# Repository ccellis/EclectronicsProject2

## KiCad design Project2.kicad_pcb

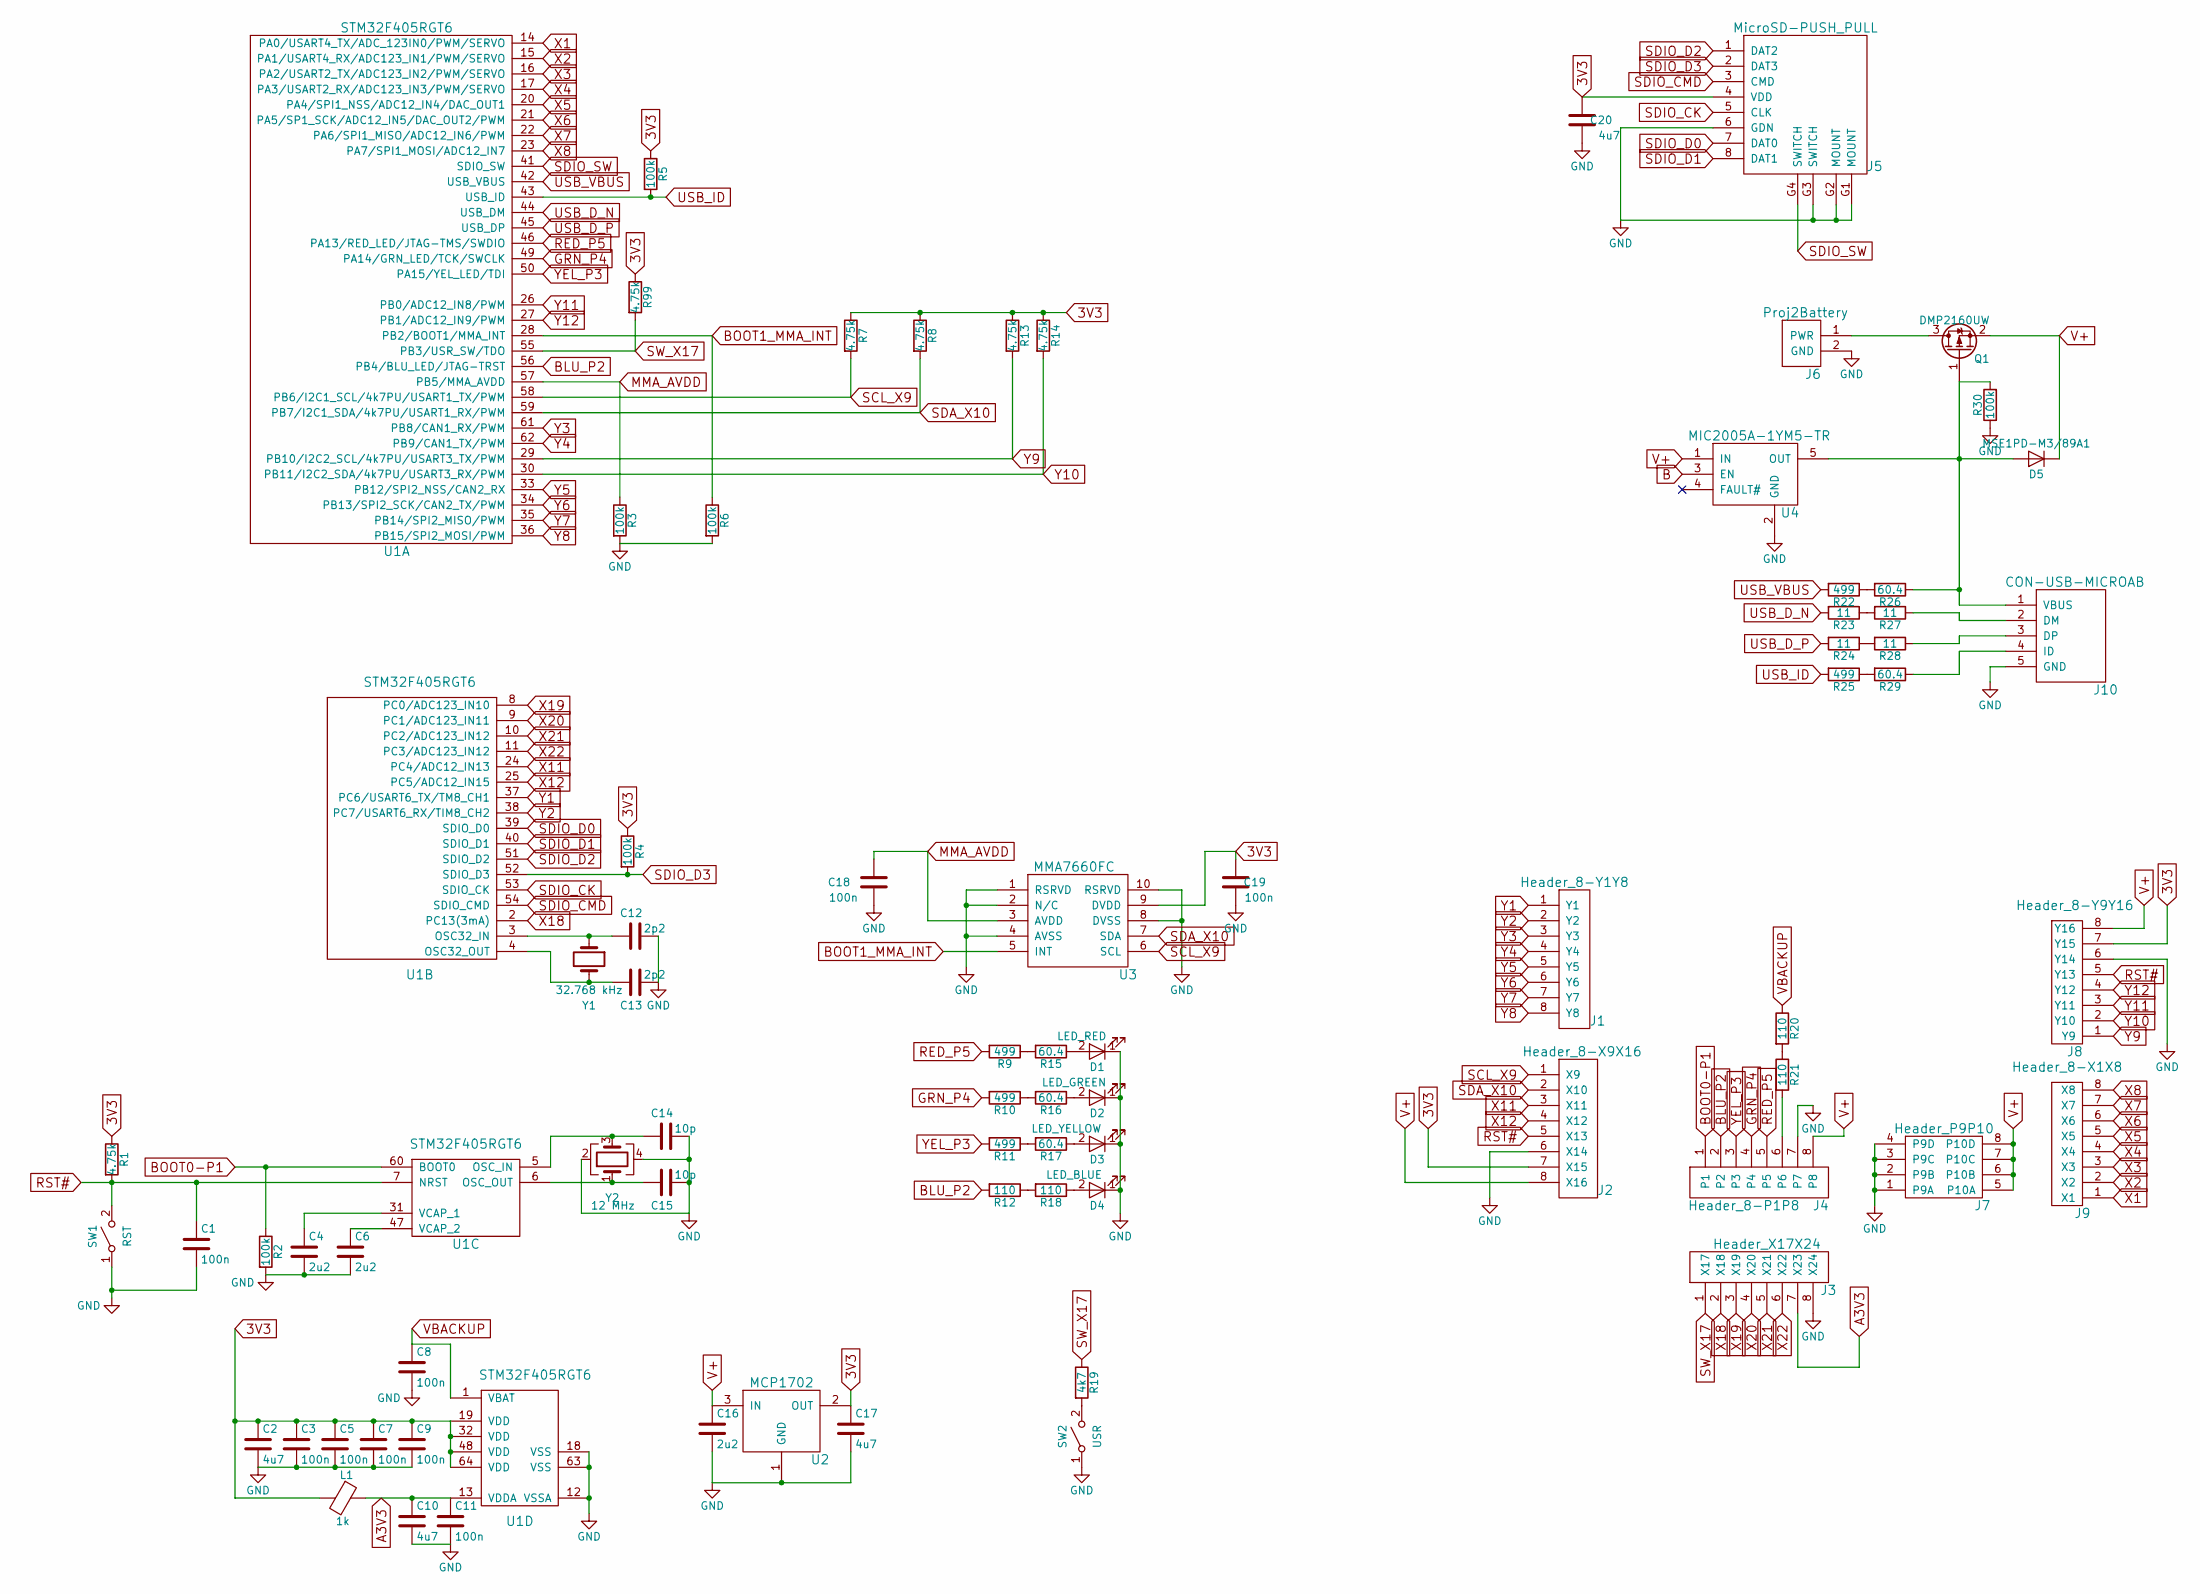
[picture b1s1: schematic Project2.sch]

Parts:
C1, C3, C5, C7, C8, C9, C11, C18, C19: 100n; C_0603
C2, C10, C17, C20: 4u7; C_0603
C4, C6, C16: 2u2; C_0603
C12, C13: 2p2; C_0603
C14, C15: 10p; C_0603
D1: LED_RED; LED_0805
D2: LED_GREEN; LED_0805
D3: LED_YELLOW; LED_0805
D4: LED_BLUE; LED_0805
D5: MSE1PD-M3/89A1; Diode
J1: Header_8-Y1Y8; 1x8_Header
J2: Header_8-X9X16; 1x8_Header
J3: Header_X17X24; 1x8_Header
J4: Header_8-P1P8; 1x8_Header
J5: MicroSD-PUSH_PULL; MicroSD
J6: Proj2Battery; Battery
J7: Header_P9P10; 2x4_Header
J8: Header_8-Y9Y16; 1x8_Header
J9: Header_8-X1X8; 1x8_Header
J10: CON-USB-MICROAB; USB_microB_2040002-1
L1: 1k; L_0603
Q1: DMP2160UW; MOSFET
R1, R7, R8, R13, R14, R99: 4.75k; R_0603
R2, R3, R4, R5, R6, R30: 100k; R_0603
R9, R10, R11, R22, R25: 499; R_0603
R12, R18, R20, R21: 110; R_0603
R15, R16, R17, R26, R29: 60.4; R_0603
R19: 4k7; R_0603
R23, R24, R27, R28: 11; R_0603
SW1: RST; Switch
SW2: USR; Switch
U1: STM32F405RGT6; MicrocontrollerFootprint
U2: MCP1702; VoltageRegulator
U3: MMA7660FC; Accelerometer
U4: MIC2005A-1YM5-TR; SOT-23-5
Y1: 32.768 kHz; Crystal_SMD_3215-2pin_3.2x1.5mm
Y2: 12 MHz; Crystal_SMD_3225-4pin_3.2x2.5mm

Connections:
3V3: C2.1, C3.1, C5.1, C7.1, C9.1, C17.1, C19.2, C20.2, J2.7 (X15), J5.4 (VDD), J8.7 (Y15), L1.2, R1.1, R4.1, R5.1, R7.1, R8.1, R13.1, R14.1, R99.1, U1.19 (VDD), U1.32 (VDD), U1.48 (VDD), U1.64 (VDD), U2.2 (OUT), U3.9 (DVDD)
A3V3: C10.1, C11.1, J3.7 (X23), L1.1, U1.13 (VDDA)
B: U4.3 (EN)
BLU_P2: J4.2, R12.2, U1.56 (PB4/BLU_LED/JTAG-TRST)
BOOT0-P1: J4.1, R2.1, U1.60 (BOOT0)
BOOT1_MMA_INT: R6.1, U1.28 (PB2/BOOT1/MMA_INT), U3.5 (INT)
GND: C1.2, C2.2, C3.2, C4.2, C5.2, C6.2, C7.2, C8.2, C9.2, C10.2, C11.2, C12.2, C13.2, C14.2, C15.2, C16.2, C17.2, C18.1, C19.1, C20.1, D1.1 (K), D2.1 (K), D3.1 (K), D4.1 (K), J2.6 (X14), J3.8 (X24), J4.7, J5.6 (GDN), J5.G1 (MOUNT), J5.G2 (MOUNT), J5.G3 (SWITCH), J6.2 (GND), J7.1 (P9A), J7.2 (P9B), J7.3 (P9C), J7.4 (P9D), J8.6 (Y14), J10.5 (GND), R2.2, R3.2, R6.2, R30.1, SW1.1 (A), SW2.1 (A), U1.12 (VSSA), U1.18 (VSS), U1.63 (VSS), U2.1 (GND), U3.1 (RSRVD), U3.2 (N/C), U3.4 (AVSS), U3.8 (DVSS), U3.10 (RSRVD), U4.2 (GND), Y2.2, Y2.4
GRN_P4: J4.4, R10.2, U1.49 (PA14/GRN_LED/TCK/SWCLK)
MMA_AVDD: C18.2, R3.1, U1.57 (PB5/MMA_AVDD), U3.3 (AVDD)
unnamed: C4.1, U1.31 (VCAP_1)
unnamed: C6.1, U1.47 (VCAP_2)
unnamed: C12.1, U1.3 (OSC32_IN), Y1.1
unnamed: C13.1, U1.4 (OSC32_OUT), Y1.2
unnamed: C14.1, U1.5 (OSC_IN), Y2.3
unnamed: C15.1, U1.6 (OSC_OUT), Y2.1
unnamed: D1.2 (A), R15.1
unnamed: D2.2 (A), R16.1
unnamed: D3.2 (A), R17.1
unnamed: D4.2 (A), R18.1
unnamed: D5.2 (A), J10.1 (VBUS), Q1.1 (G), R26.1, R30.2, U4.5 (OUT)
unnamed: J4.6, R21.2
unnamed: J6.1 (PWR), Q1.3 (D)
unnamed: J10.2 (DM), R27.1
unnamed: J10.3 (DP), R28.1
unnamed: J10.4 (ID), R29.1
unnamed: R10.1, R16.2
unnamed: R11.1, R17.2
unnamed: R12.1, R18.2
unnamed: R9.1, R15.2
unnamed: R19.2, SW2.2 (B)
unnamed: R20.2, R21.1
unnamed: R22.1, R26.2
unnamed: R23.1, R27.2
unnamed: R24.1, R28.2
unnamed: R25.1, R29.2
RED_P5: J4.5, R9.2, U1.46 (PA13/RED_LED/JTAG-TMS/SWDIO)
RST#: C1.1, J2.5 (X13), J8.5 (Y13), R1.2, SW1.2 (B), U1.7 (NRST)
SCL_X9: J2.1 (X9), R7.2, U1.58 (PB6/I2C1_SCL/4k7PU/USART1_TX/PWM), U3.6 (SCL)
SDA_X10: J2.2 (X10), R8.2, U1.59 (PB7/I2C1_SDA/4k7PU/USART1_RX/PWM), U3.7 (SDA)
SDIO_CK: J5.5 (CLK), U1.53 (SDIO_CK)
SDIO_CMD: J5.3 (CMD), U1.54 (SDIO_CMD)
SDIO_D0: J5.7 (DAT0), U1.39 (SDIO_D0)
SDIO_D1: J5.8 (DAT1), U1.40 (SDIO_D1)
SDIO_D2: J5.1 (DAT2), U1.51 (SDIO_D2)
SDIO_D3: J5.2 (DAT3), R4.2, U1.52 (SDIO_D3)
SDIO_SW: J5.G4 (SWITCH), U1.41 (SDIO_SW)
SW_X17: J3.1 (X17), R19.1, R99.2, U1.55 (PB3/USR_SW/TDO)
USB_D_N: R23.2, U1.44 (USB_DM)
USB_D_P: R24.2, U1.45 (USB_DP)
USB_ID: R5.2, R25.2, U1.43 (USB_ID)
USB_VBUS: R22.2, U1.42 (USB_VBUS)
V+: C16.1, D5.1 (K), J2.8 (X16), J4.8, J7.5 (P10A), J7.6 (P10B), J7.7 (P10C), J7.8 (P10D), J8.8 (Y16), Q1.2 (S), U2.3 (IN), U4.1 (IN)
VBACKUP: C8.1, R20.1, U1.1 (VBAT)
X1: J9.1 (X1), U1.14 (PA0/USART4_TX/ADC_123IN0/PWM/SERVO)
X2: J9.2 (X2), U1.15 (PA1/USART4_RX/ADC123_IN1/PWM/SERVO)
X3: J9.3 (X3), U1.16 (PA2/USART2_TX/ADC123_IN2/PWM/SERVO)
X4: J9.4 (X4), U1.17 (PA3/USART2_RX/ADC123_IN3/PWM/SERVO)
X5: J9.5 (X5), U1.20 (PA4/SPI1_NSS/ADC12_IN4/DAC_OUT1)
X6: J9.6 (X6), U1.21 (PA5/SP1_SCK/ADC12_IN5/DAC_OUT2/PWM)
X7: J9.7 (X7), U1.22 (PA6/SPI1_MISO/ADC12_IN6/PWM)
X8: J9.8 (X8), U1.23 (PA7/SPI1_MOSI/ADC12_IN7)
X11: J2.3 (X11), U1.24 (PC4/ADC12_IN13)
X12: J2.4 (X12), U1.25 (PC5/ADC12_IN15)
X18: J3.2 (X18), U1.2 (PC13(3mA))
X19: J3.3 (X19), U1.8 (PC0/ADC123_IN10)
X20: J3.4 (X20), U1.9 (PC1/ADC123_IN11)
X21: J3.5 (X21), U1.10 (PC2/ADC123_IN12)
X22: J3.6 (X22), U1.11 (PC3/ADC123_IN12)
Y1: J1.1 (Y1), U1.37 (PC6/USART6_TX/TM8_CH1)
Y2: J1.2 (Y2), U1.38 (PC7/USART6_RX/TIM8_CH2)
Y3: J1.3 (Y3), U1.61 (PB8/CAN1_RX/PWM)
Y4: J1.4 (Y4), U1.62 (PB9/CAN1_TX/PWM)
Y5: J1.5 (Y5), U1.33 (PB12/SPI2_NSS/CAN2_RX)
Y6: J1.6 (Y6), U1.34 (PB13/SPI2_SCK/CAN2_TX/PWM)
Y7: J1.7 (Y7), U1.35 (PB14/SPI2_MISO/PWM)
Y8: J1.8 (Y8), U1.36 (PB15/SPI2_MOSI/PWM)
Y9: J8.1 (Y9), R13.2, U1.29 (PB10/I2C2_SCL/4k7PU/USART3_TX/PWM)
Y10: J8.2 (Y10), R14.2, U1.30 (PB11/I2C2_SDA/4k7PU/USART3_RX/PWM)
Y11: J8.3 (Y11), U1.26 (PB0/ADC12_IN8/PWM)
Y12: J8.4 (Y12), U1.27 (PB1/ADC12_IN9/PWM)
YEL_P3: J4.3, R11.2, U1.50 (PA15/YEL_LED/TDI)

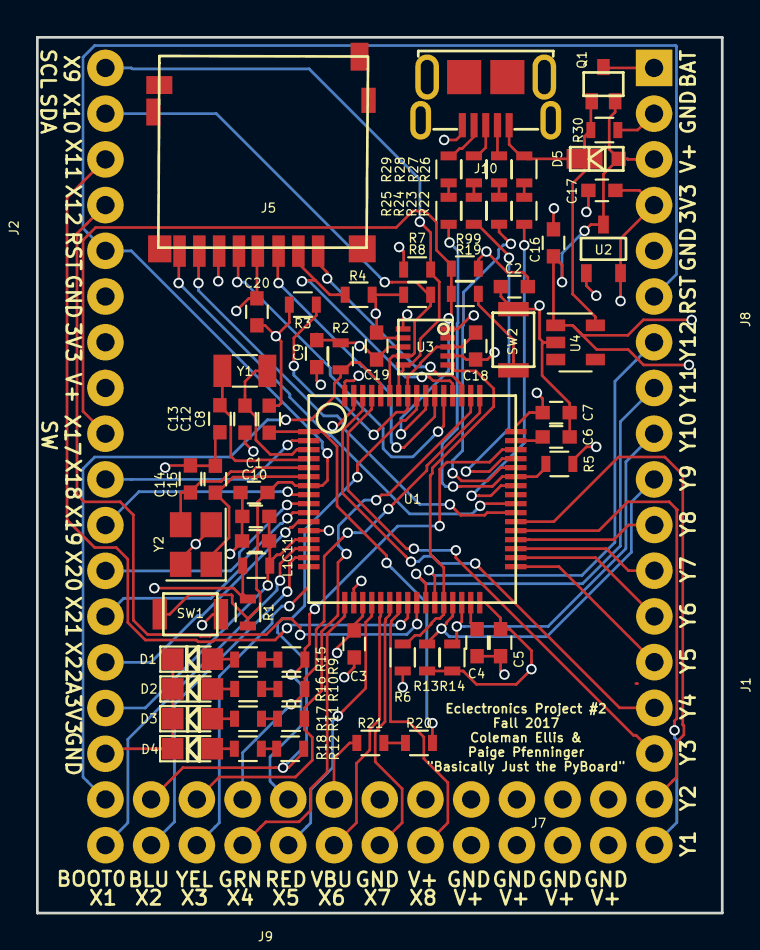
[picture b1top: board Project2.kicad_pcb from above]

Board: 4 copper layers, 38.0 x 48.7 mm, 76 parts (0 on the bottom side), 79 nets.

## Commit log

2017-09-24 Initial Upload of Kicad files w/ symbols for STM32F405RGT6
2017-09-25 Added parts
    Added parts
2017-09-25 Started work on big schematic
2017-09-25 gitignore .bak
2017-09-26 Added more components
2017-09-26 Once again trying to .gitignore .bak files...
2017-09-27 Finished (?) the schematic
2017-09-28 A couple schematic changes, footprint library, and microcontroller footprint
2017-09-29 added some stuff
2017-09-29 changed things
2017-09-29 Finished footprints
2017-09-29 Ignoring fp-lib-table
2017-09-29 Consolidated footprints to one library
2017-10-04 Finished schematic, created a couple footprints, started layout
2017-10-05 Almost the whole layout
2017-10-05 ALL THE SIGNAL PINS
2017-10-08 Finished Pass 1
2017-10-12 Finished
